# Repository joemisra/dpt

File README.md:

# dsp.coffee dpt - multifunction electron temple

** Fully built DPT module is currently unavailable, populated boards + panels are though - currently available at https://dsp.coffee/. In stock as of 2/17/2023. **

electrosmith daisy patch submodule based development platform

* 8 pots normalled to 0V - +5V.
* 8 CV in, this breaks normalled connection and pot acts as an attenuator.
* 2 gate in
* 2 gate out
* High fidelity stereo in/out (Daisy Patch Submodule uses the PCM3080 codec).
* 2 12-bit CV out from Daisy Patch Submodule, scaled to -5v to 10v
* 4 12-bit CV (or lofi audio w/ some hacking) from external DAC7554, scaled to -7v to 7v.
* TRS MIDI in/out (midi in uses lpzw auto-sensing circuit for type a/b)
* SD card slot.
* Expander header on the back for +5v, +3v3, SPI, UART, I2C, and USB connections. [Two expanders have been prototyped now, one with two tact switches and USB port, one with LED controller + 5 RGB leds and 4 tact switches]

Output scaling circuits for DAC7554 and TRS MIDI are based
on portions of https://github.com/plinkysynth/plinky-expander

Additional References
* https://www.electro-smith.com/daisy/patch-sm
* https://electro-smith.github.io/DaisySP/index.html
* https://electro-smith.github.io/libDaisy/index.html

Thx
* https://github.com/makingsoundmachines
* https://github.com/thisisnotrocketscience
* https://github.com/mmalex

BOM

|Designator|Package                                                                                                                                                                                                                 |Quantity                                   |Designation|Supplier and ref      |
|----------|------------------------------------------------------------------------------------------------------------------------------------------------------------------------------------------------------------------------|-------------------------------------------|-----------|----------------------|
|LED3,LED4 |3mm LED                                                                                                                                                                                                                 |2                                          ||                      |
|J*|Mono Thonkiconn                                                                                                                                                                                                         |22 
|JMIDIIN, JMIDIOUT|Stereo (Green) Thonkiconn                                                                                                                                                                                                         |2                    
|VRCV*|9mm Potentiometer (Alpha / Alps)                                                                                                                                                                                        |8                                          |10K        |                      |
|D4,D6,D5,D3,D8,D7|3mm LED (Bipolar Red / Green)                                                                                                                                                                                           |6                                          |LED_Dual_Bidirectional|Tayda                 |
|U_SDCARD1 |VERT_MICROSD_CENTERED                                                                                                                                                                                                   |1                                          || Mouser 945-PJS008U-3000-0 / Thonk |
|U9        |Electrosmith Daisy Patch Submodule                                                                                                                                                                                      |1                                          |ES_DAISY_PATCH_SM_REV1|                      | https://www.electro-smith.com/daisy/patch-sm
|R36,R35,R18,R16,
R17,R19|0603                                                                                                                                                                                                       |6                                          |1k         |                      |
|U11,U5,U10,U3,
U6,U4|SOIC-8                                                                                                                                                                                            |6                                          |TL072      |                      |
|C5,C4     |0603                                                                                                                                                                          |2                                          |100n       |                      |
|R9,R11,R10,R8|0603                                                                                                                                                                                                   |4                                          |56k        |                      |
|C2,C3     |C_Elec_4x5.4                                                                                                                                                                                                            |2                                          |47u        |                      |
|J_I2C1    |2x03 2.54mm_Vertical                                                                                                                                                                                         |1                                          ||                      |
|C11,C12,C13,C10,C18,C17|0603                                                                                                                                                                                                      |6                                          |1n         |                      |
|R22,R4,R7,R20,R29,
R30,R2,R6,R5|0603                                                                                                                                                                                                     |9                                          |10k        |                      |
|C14,C16,C6,C7,
C1,C8,C15,C9|0603                                                                                                                                                                                                     |8                                          |100n       |                      |
|R26,R34,R15,R24,
R33,R28,R27,R14,
R13,R25,R12|0603                                                                                                                                                                                                      |11                                         |220R       |                      |
|J14       |2x05 P2.54mm Vertical                                                                                                                                                                                         |1                                          ||                      |
|U2        |DAC7554IDGS                                                                                                                                                                                                  |1                                          ||                      |
|R32,R31   |0603                                                                                                                                                                                                      |2                                          |30k        |                      |
|R23,R21   |0603                                                                                                                                                                                                      |2                                          |4.7k       |                      |
|U8        |HCPL-0631 SOIC-8                                                                                                                                                                                               |1                                          |  |                      |
|U1        |LM4040DBZ-2.5 SOT-23                                                                                                                                                                                                                  |1                                          ||                      |
|J_EXPANDER2|2x08 P2.54mm Vertical                                                                                                                                                                                         |1                                          |USB_SPI_MUX_EXPANDER|                      |
|R1        |0603                                                                                                                                                                                                      |1                                          |3k         |                      |
|D2,D1     |1N1517 SOD-323                                                                                                                                                                                                               |2                                          |     |                      |
|R3        |0603                                                                                                                                                                                                      |1                                          |7.5k       |                      |
|U7        |SN74LVC1G17DBV SOT-23-5                                                                                                                                                                                                                |1                                          ||                      |

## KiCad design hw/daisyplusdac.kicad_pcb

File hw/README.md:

* Ultimately, assemble this however is most comfortable, but ensure that everything is flush.

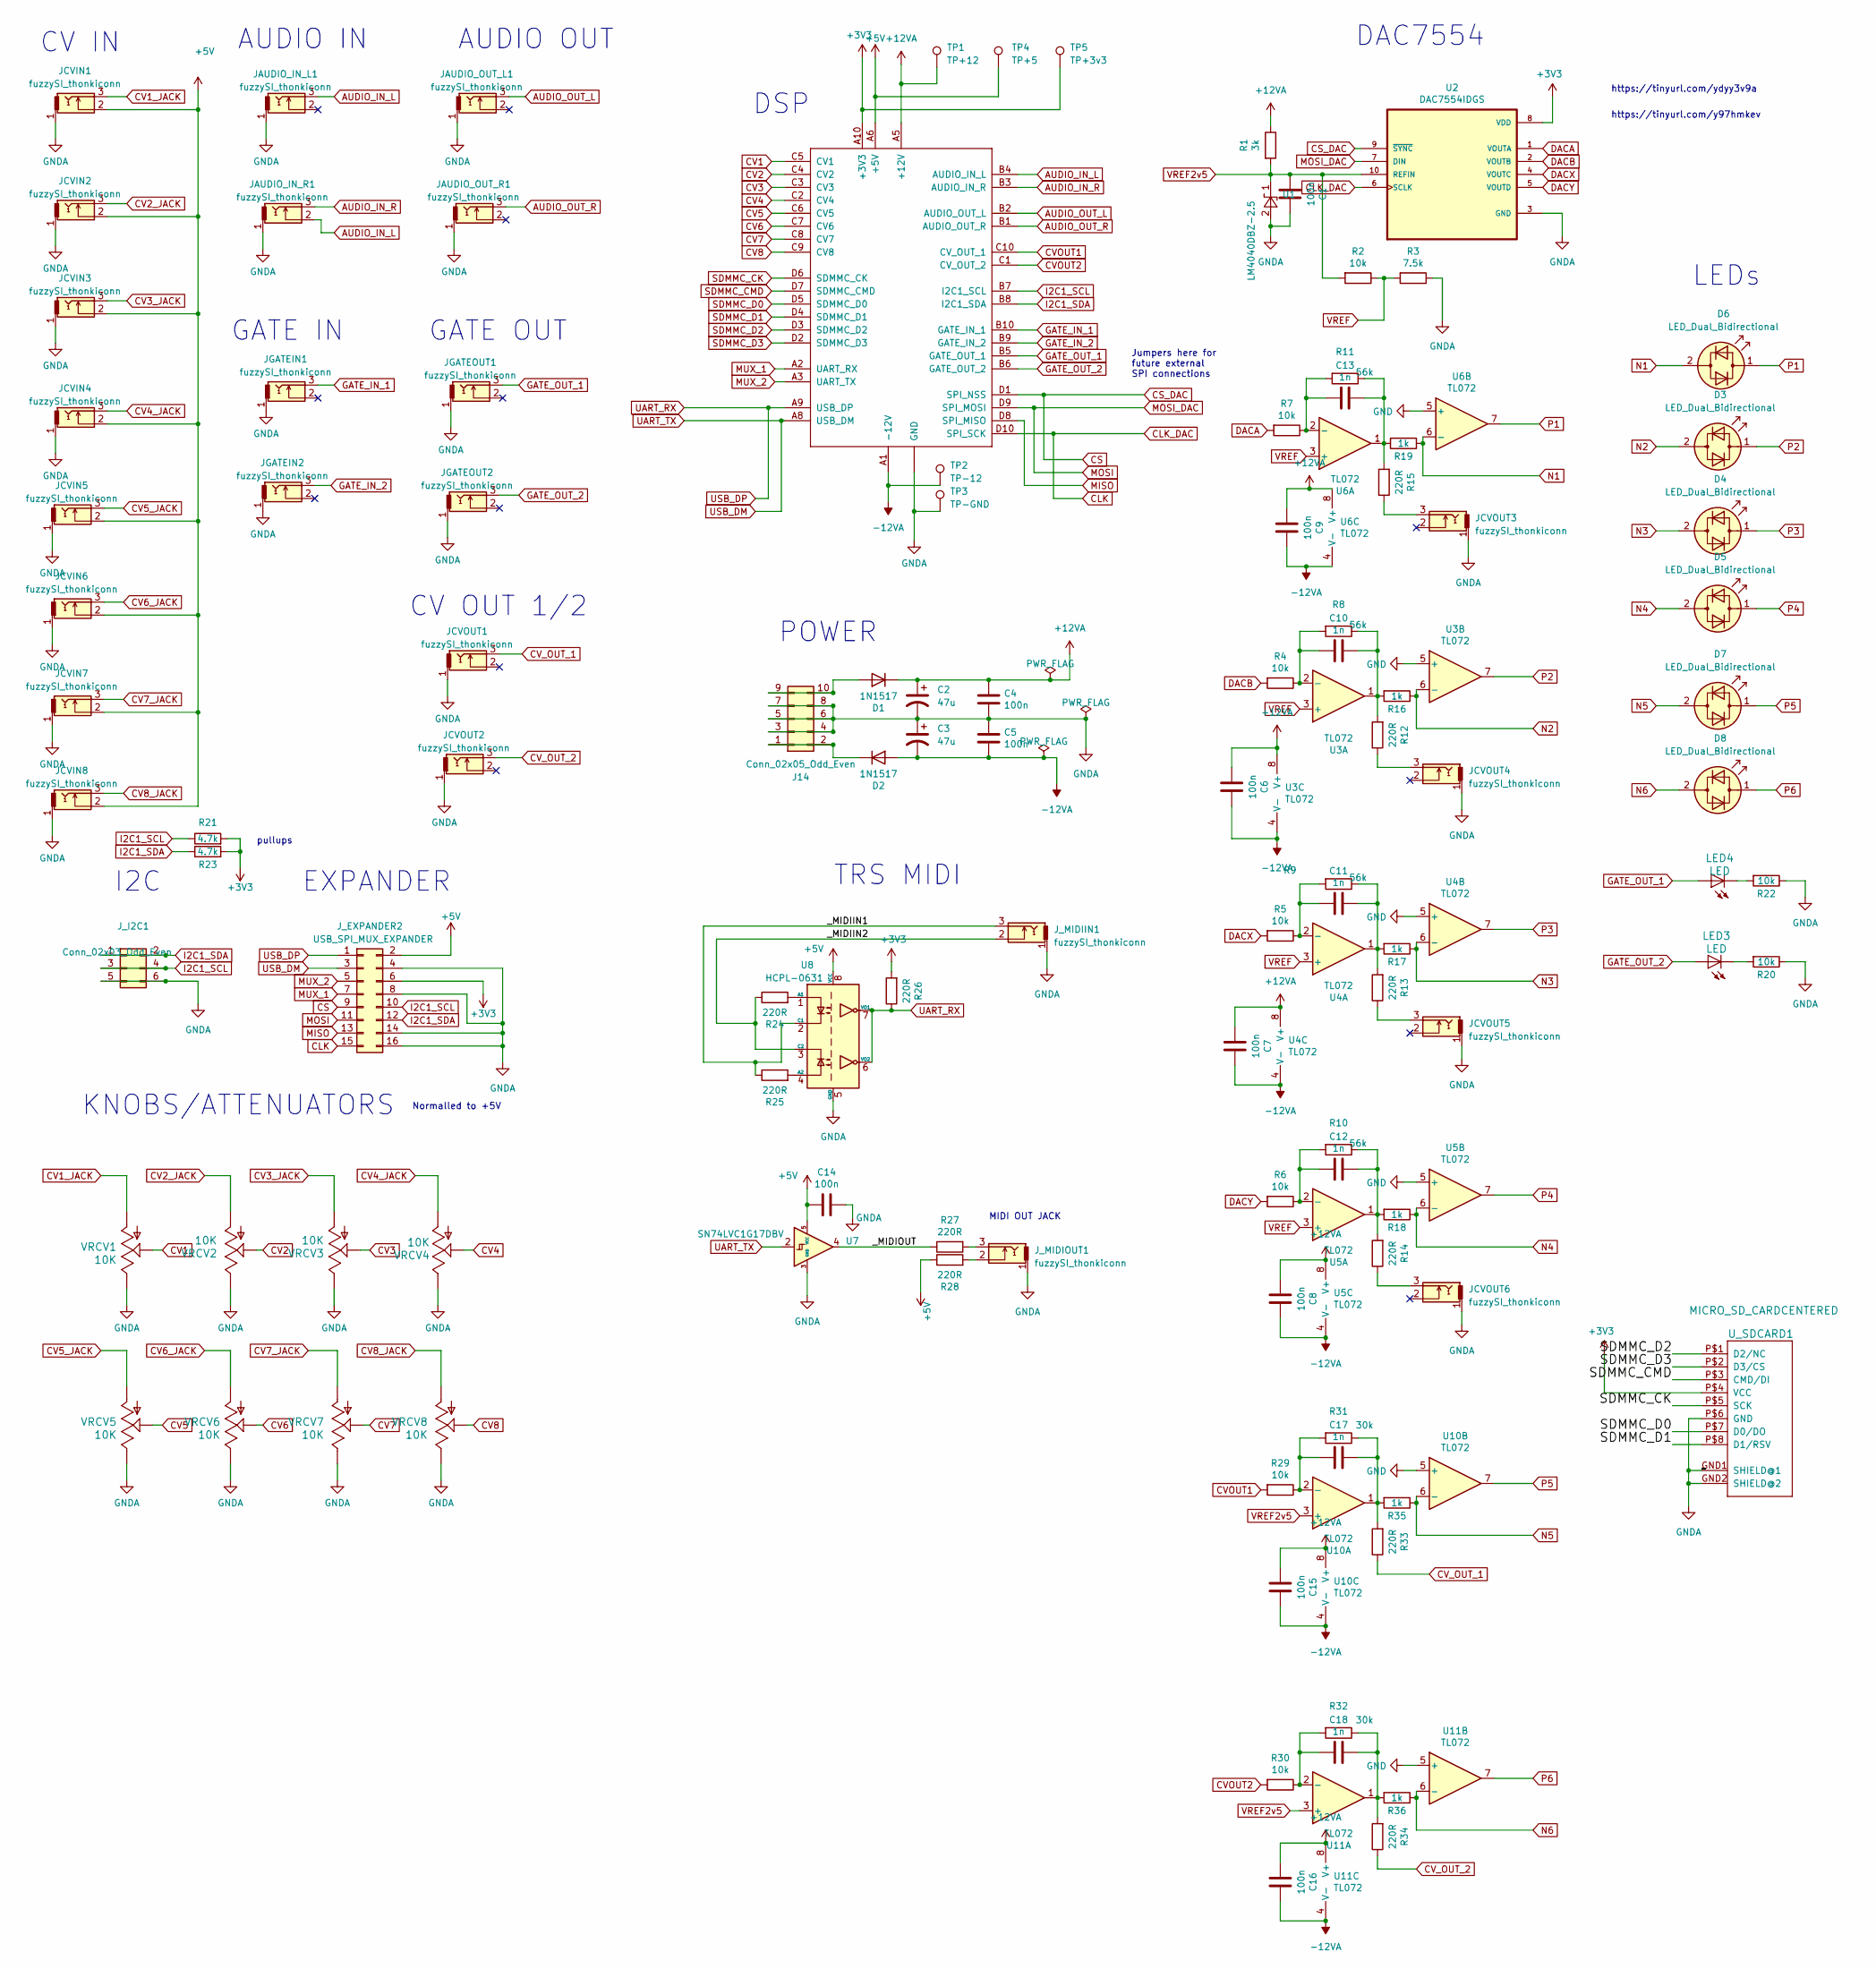
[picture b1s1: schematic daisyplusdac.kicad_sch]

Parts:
C1, C6, C7, C8, C9, C14, C15, C16: 100n; C_0603_1608Metric
C2, C3: 47u; C_Elec_4x5.4
C4, C5: 100n; C_0603_1608Metric_Pad1.08x0.95mm_HandSolder
C10, C11, C12, C13, C17, C18: 1n; C_0603_1608Metric
D1, D2: 1N1517; D_SOD-323
D3, D4, D5, D6, D7, D8: LED_Dual_Bidirectional; LED_D3.0mm
J14: Conn_02x05_Odd_Even; PinHeader_2x05_P2.54mm_Vertical
JAUDIO_IN_L1: fuzzySI_thonkiconn; thonkiconn_fuzzySi
JAUDIO_IN_R1: fuzzySI_thonkiconn; thonkiconn_fuzzySi
JAUDIO_OUT_L1: fuzzySI_thonkiconn; thonkiconn_fuzzySi
JAUDIO_OUT_R1: fuzzySI_thonkiconn; thonkiconn_fuzzySi
JCVIN1, JCVIN2, JCVIN3, JCVIN4, JCVIN5, JCVIN6, JCVIN7, JCVIN8: fuzzySI_thonkiconn; thonkiconn_fuzzySi
JCVOUT1, JCVOUT2, JCVOUT3, JCVOUT4, JCVOUT5, JCVOUT6: fuzzySI_thonkiconn; thonkiconn_fuzzySi
JGATEIN1, JGATEIN2: fuzzySI_thonkiconn; thonkiconn_fuzzySi
JGATEOUT1, JGATEOUT2: fuzzySI_thonkiconn; thonkiconn_fuzzySi
J_EXPANDER2: USB_SPI_MUX_EXPANDER; PinHeader_2x08_P2.54mm_Vertical
J_I2C1: Conn_02x03_Odd_Even; PinHeader_2x03_P2.54mm_Vertical
J_MIDIIN1: fuzzySI_thonkiconn; thonkiconn_fuzzySi
J_MIDIOUT1: fuzzySI_thonkiconn; thonkiconn_fuzzySi
LED3, LED4: LED
R1: 3k; R_0603_1608Metric
R2, R4, R5, R6, R7, R20, R22, R29, R30: 10k; R_0603_1608Metric
R3: 7.5k; R_0603_1608Metric
R8, R9, R10, R11: 56k; R_0603_1608Metric
R12, R13, R14, R15, R24, R25, R26, R27, R28, R33, R34: 220R; R_0603_1608Metric
R16, R17, R18, R19, R35, R36: 1k; R_0603_1608Metric
R21, R23: 4.7k; R_0603_1608Metric
R31, R32: 30k; R_0603_1608Metric
TP1: TP+12; TestPoint_Keystone_5000-5004_Miniature
TP2: TP-12; TestPoint_Keystone_5000-5004_Miniature
TP3: TP-GND; TestPoint_Keystone_5000-5004_Miniature
TP4: TP+5; TestPoint_Keystone_5000-5004_Miniature
TP5: TP+3v3; TestPoint_Keystone_5000-5004_Miniature
U1: LM4040DBZ-2.5; SOT-23
U2: DAC7554IDGS; MSOP-10_3x3mm_P0.5mm
U3, U4, U5, U6, U10, U11: TL072; SOIC-8_3.9x4.9mm_P1.27mm
U7: SN74LVC1G17DBV; SOT-23-5
U8: HCPL-0631; SOIC-8_3.9x4.9mm_P1.27mm
U9: ES_DAISY_PATCH_SM_REV1
U_SDCARD1: MICRO_SD_CARDCENTERED; VERT_MICROSD_CENTERED
VRCV1, VRCV2, VRCV3, VRCV4, VRCV5, VRCV6, VRCV7, VRCV8: 10K; Potentiometer_Alps_RK09K_Single_Vertical

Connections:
+3V3: J_EXPANDER2.6, R21.2, R23.2, R26.2, TP5.1, U2.8 (VDD), U9.A10 (+3V3), U_SDCARD1.P$4 (VCC)
+5V: C14.1, JCVIN1.2, JCVIN2.2, JCVIN3.2, JCVIN4.2, JCVIN5.2, JCVIN6.2, JCVIN7.2, JCVIN8.2, J_EXPANDER2.2, R28.1, TP4.1, U7.5 (VCC), U8.8 (VCC), U9.A6 (+5V)
+12VA: C2.1, C4.1, C6.1, C7.1, C8.1, C9.1, C15.1, C16.1, D1.1 (K), R1.1, TP1.1, U3.8 (V+), U4.8 (V+), U5.8 (V+), U6.8 (V+), U9.A5 (+12V), U10.8 (V+), U11.8 (V+)
-12VA: C3.2, C5.2, C6.2, C7.2, C8.2, C9.2, C15.2, C16.2, D2.2 (A), TP2.1, U3.4 (V-), U4.4 (V-), U5.4 (V-), U6.4 (V-), U9.A1 (-12V), U10.4 (V-), U11.4 (V-)
/_MIDIIN1: J_MIDIIN1.3, R25.1, U8.2 (C1)
/_MIDIIN2: J_MIDIIN1.2, R24.1, U8.3 (C2)
/_MIDIOUT: R27.1, U7.4
AUDIO_IN_L: JAUDIO_IN_L1.3, JAUDIO_IN_R1.2, U9.B4 (AUDIO_IN_L)
AUDIO_IN_R: JAUDIO_IN_R1.3, U9.B3 (AUDIO_IN_R)
AUDIO_OUT_L: JAUDIO_OUT_L1.3, U9.B2 (AUDIO_OUT_L)
AUDIO_OUT_R: JAUDIO_OUT_R1.3, U9.B1 (AUDIO_OUT_R)
CLK: J_EXPANDER2.15, U2.6 (SCLK), U9.D10 (SPI_SCK)
CS: J_EXPANDER2.9, U2.9 (~SYNC), U9.D1 (SPI_NSS)
CV1: U9.C5 (CV1), VRCV1.2
CV1_JACK: JCVIN1.3, VRCV1.1
CV2: U9.C4 (CV2), VRCV2.2
CV2_JACK: JCVIN2.3, VRCV2.1
CV3: U9.C3 (CV3), VRCV3.2
CV3_JACK: JCVIN3.3, VRCV3.1
CV4: U9.C2 (CV4), VRCV4.2
CV4_JACK: JCVIN4.3, VRCV4.1
CV5: U9.C6 (CV5), VRCV5.2
CV5_JACK: JCVIN5.3, VRCV5.1
CV6: U9.C7 (CV6), VRCV6.2
CV6_JACK: JCVIN6.3, VRCV6.1
CV7: U9.C8 (CV7), VRCV7.2
CV7_JACK: JCVIN7.3, VRCV7.1
CV8: U9.C9 (CV8), VRCV8.2
CV8_JACK: JCVIN8.3, VRCV8.1
CVOUT1: R29.2, U9.C10 (CV_OUT_1)
CVOUT2: R30.2, U9.C1 (CV_OUT_2)
CV_OUT_1: JCVOUT1.3, R33.1
CV_OUT_2: JCVOUT2.3, R34.1
DACA: R7.2, U2.1 (VOUTA)
DACB: R4.2, U2.2 (VOUTB)
DACX: R5.2, U2.4 (VOUTC)
DACY: R6.2, U2.5 (VOUTD)
GATE_IN_1: JGATEIN1.3, U9.B10 (GATE_IN_1)
GATE_IN_2: JGATEIN2.3, U9.B9 (GATE_IN_2)
GATE_OUT_1: JGATEOUT1.3, LED4.A, U9.B5 (GATE_OUT_1)
GATE_OUT_2: JGATEOUT2.3, LED3.A, U9.B6 (GATE_OUT_2)
GND: C1.1, C2.2, C3.1, C4.2, C5.1, C14.2, J14.3, J14.4, J14.5, J14.6, J14.7, J14.8, JAUDIO_IN_L1.1, JAUDIO_IN_R1.1, JAUDIO_OUT_L1.1, JAUDIO_OUT_R1.1, JCVIN1.1, JCVIN2.1, JCVIN3.1, JCVIN4.1, JCVIN5.1, JCVIN6.1, JCVIN7.1, JCVIN8.1, JCVOUT1.1, JCVOUT2.1, JCVOUT3.1, JCVOUT4.1, JCVOUT5.1, JCVOUT6.1, JGATEIN1.1, JGATEIN2.1, JGATEOUT1.1, JGATEOUT2.1, J_EXPANDER2.4, J_EXPANDER2.8, J_EXPANDER2.14, J_EXPANDER2.16, J_I2C1.5, J_I2C1.6, J_MIDIIN1.1, J_MIDIOUT1.1, R3.1, R20.1, R22.1, TP3.1, U1.2 (A), U2.3 (GND), U3.5 (+), U4.5 (+), U5.5 (+), U6.5 (+), U7.3 (GND), U8.5 (GND), U9.A4 (GND), U9.A7 (GND), U10.5 (+), U11.5 (+), U_SDCARD1.GND1 (SHIELD@1), U_SDCARD1.GND2 (SHIELD@2), U_SDCARD1.P$6 (GND), VRCV1.3, VRCV2.3, VRCV3.3, VRCV4.3, VRCV5.3, VRCV6.3, VRCV7.3, VRCV8.3
I2C1_SCL: J_EXPANDER2.10, J_I2C1.3, J_I2C1.4, R21.1, U9.B7 (I2C1_SCL)
I2C1_SDA: J_EXPANDER2.12, J_I2C1.1, J_I2C1.2, R23.1, U9.B8 (I2C1_SDA)
MISO: J_EXPANDER2.13, U9.D8 (SPI_MISO)
MOSI: J_EXPANDER2.11, U2.7 (DIN), U9.D9 (SPI_MOSI)
MUX_1: J_EXPANDER2.7, U9.A2 (UART_RX)
MUX_2: J_EXPANDER2.5, U9.A3 (UART_TX)
N1: D6.2 (AK), R19.1, U6.6 (-)
N2: D3.2 (AK), R16.1, U3.6 (-)
N3: D4.2 (AK), R17.1, U4.6 (-)
N4: D5.2 (AK), R18.1, U5.6 (-)
N5: D7.2 (AK), R35.1, U10.6 (-)
N6: D8.2 (AK), R36.1, U11.6 (-)
unnamed: C10.1, R8.1, R12.2, R16.2, U3.1
unnamed: C11.1, R9.1, R13.2, R17.2, U4.1
unnamed: C12.1, R10.1, R14.2, R18.2, U5.1
unnamed: C13.1, R11.1, R15.2, R19.2, U6.1
unnamed: C17.1, R31.1, R33.2, R35.2, U10.1
unnamed: C18.1, R32.1, R34.2, R36.2, U11.1
unnamed: D1.2 (A), J14.9, J14.10
unnamed: D2.1 (K), J14.1, J14.2
unnamed: JCVOUT3.3, R15.1
unnamed: JCVOUT4.3, R12.1
unnamed: JCVOUT5.3, R13.1
unnamed: JCVOUT6.3, R14.1
unnamed: J_MIDIOUT1.2, R28.2
unnamed: J_MIDIOUT1.3, R27.2
unnamed: LED3.K (C), R20.2
unnamed: LED4.K (C), R22.2
unnamed: C10.2, R4.1, R8.2, U3.2 (-)
unnamed: C11.2, R5.1, R9.2, U4.2 (-)
unnamed: C12.2, R6.1, R10.2, U5.2 (-)
unnamed: C13.2, R7.1, R11.2, U6.2 (-)
unnamed: R24.2, U8.1 (A1)
unnamed: R25.2, U8.4 (A2)
unnamed: C17.2, R29.1, R31.2, U10.2 (-)
unnamed: C18.2, R30.1, R32.2, U11.2 (-)
P1: D6.1 (KA), U6.7
P2: D3.1 (KA), U3.7
P3: D4.1 (KA), U4.7
P4: D5.1 (KA), U5.7
P5: D7.1 (KA), U10.7
P6: D8.1 (KA), U11.7
SDMMC_CK: U9.D6 (SDMMC_CK), U_SDCARD1.P$5 (SCK)
SDMMC_CMD: U9.D7 (SDMMC_CMD), U_SDCARD1.P$3 (CMD/DI)
SDMMC_D0: U9.D5 (SDMMC_D0), U_SDCARD1.P$7 (D0/DO)
SDMMC_D1: U9.D4 (SDMMC_D1), U_SDCARD1.P$8 (D1/RSV)
SDMMC_D2: U9.D3 (SDMMC_D2), U_SDCARD1.P$1 (D2/NC)
SDMMC_D3: U9.D2 (SDMMC_D3), U_SDCARD1.P$2 (D3/CS)
UART_RX: J_EXPANDER2.1, R26.1, U8.6 (VO2), U8.7 (VO1), U9.A9 (USB_DP)
UART_TX: J_EXPANDER2.3, U7.2, U9.A8 (USB_DM)
VREF: R2.1, R3.2, U3.3 (+), U4.3 (+), U5.3 (+), U6.3 (+)
VREF2v5: C1.2, R1.2, R2.2, U1.1 (K), U2.10 (REFIN), U10.3 (+), U11.3 (+)

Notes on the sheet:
DSP
CV IN
EXPANDER
AUDIO OUT
Jumpers here for future external SPI connections
POWER
DAC7554
TRS MIDI
MIDI OUT JACK
pullups
https://tinyurl.com/ydyy3v9a
KNOBS/ATTENUATORS
I2C
https://tinyurl.com/y97hmkev
CV OUT 1/2
GATE OUT
GATE IN
AUDIO IN
LEDs
Normalled to +5V

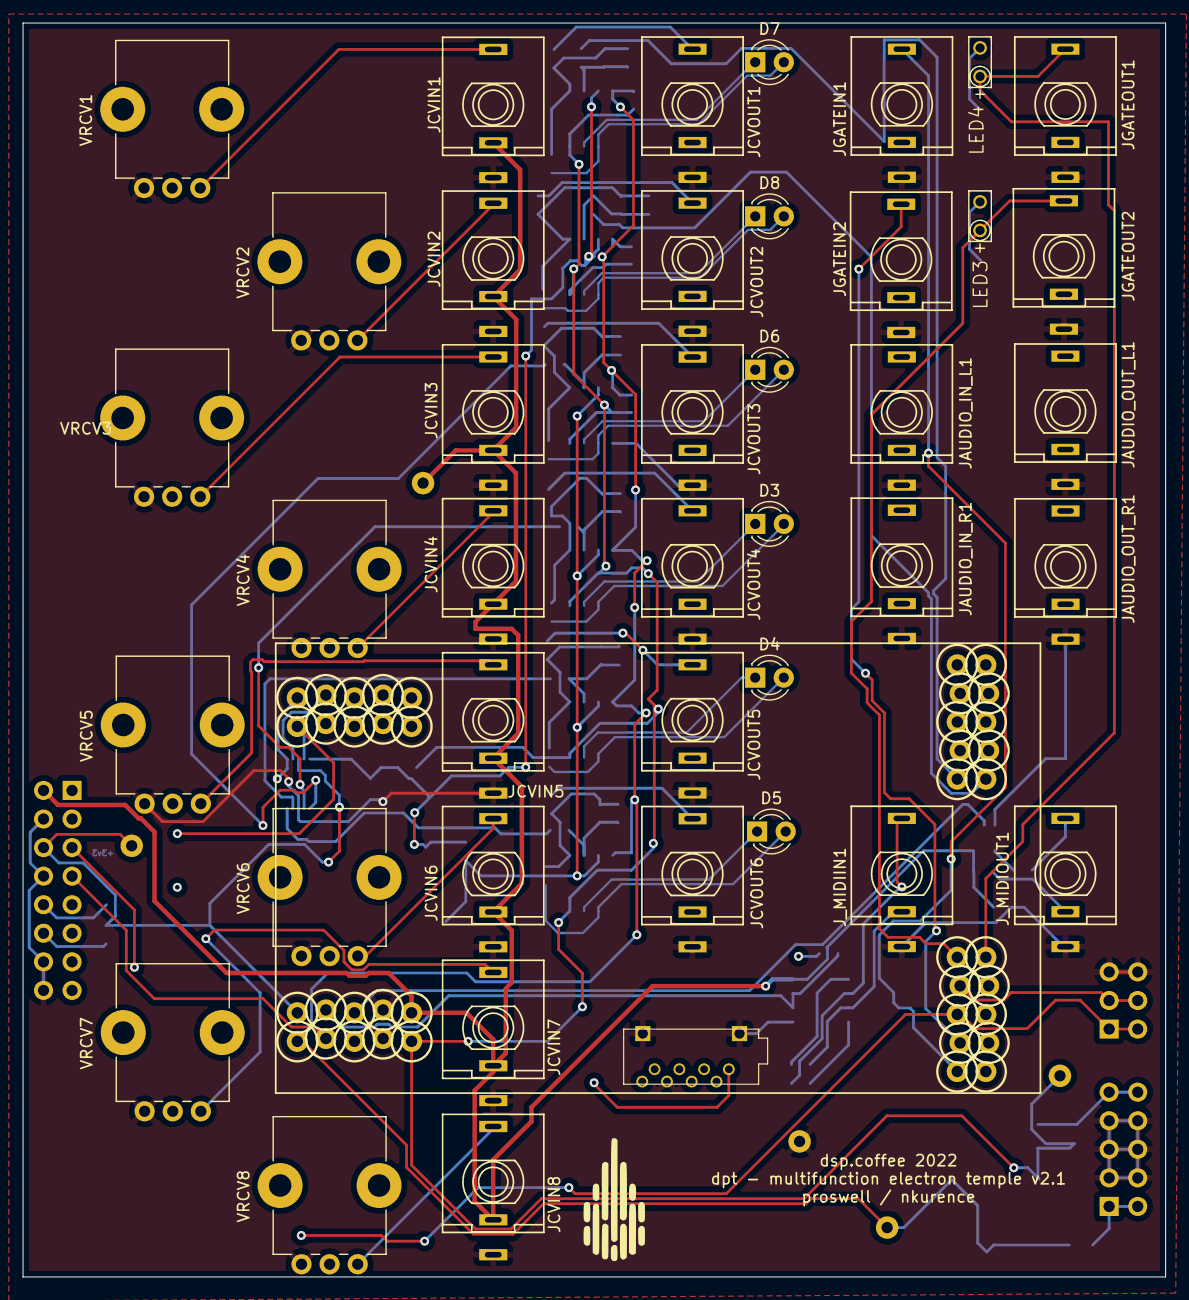
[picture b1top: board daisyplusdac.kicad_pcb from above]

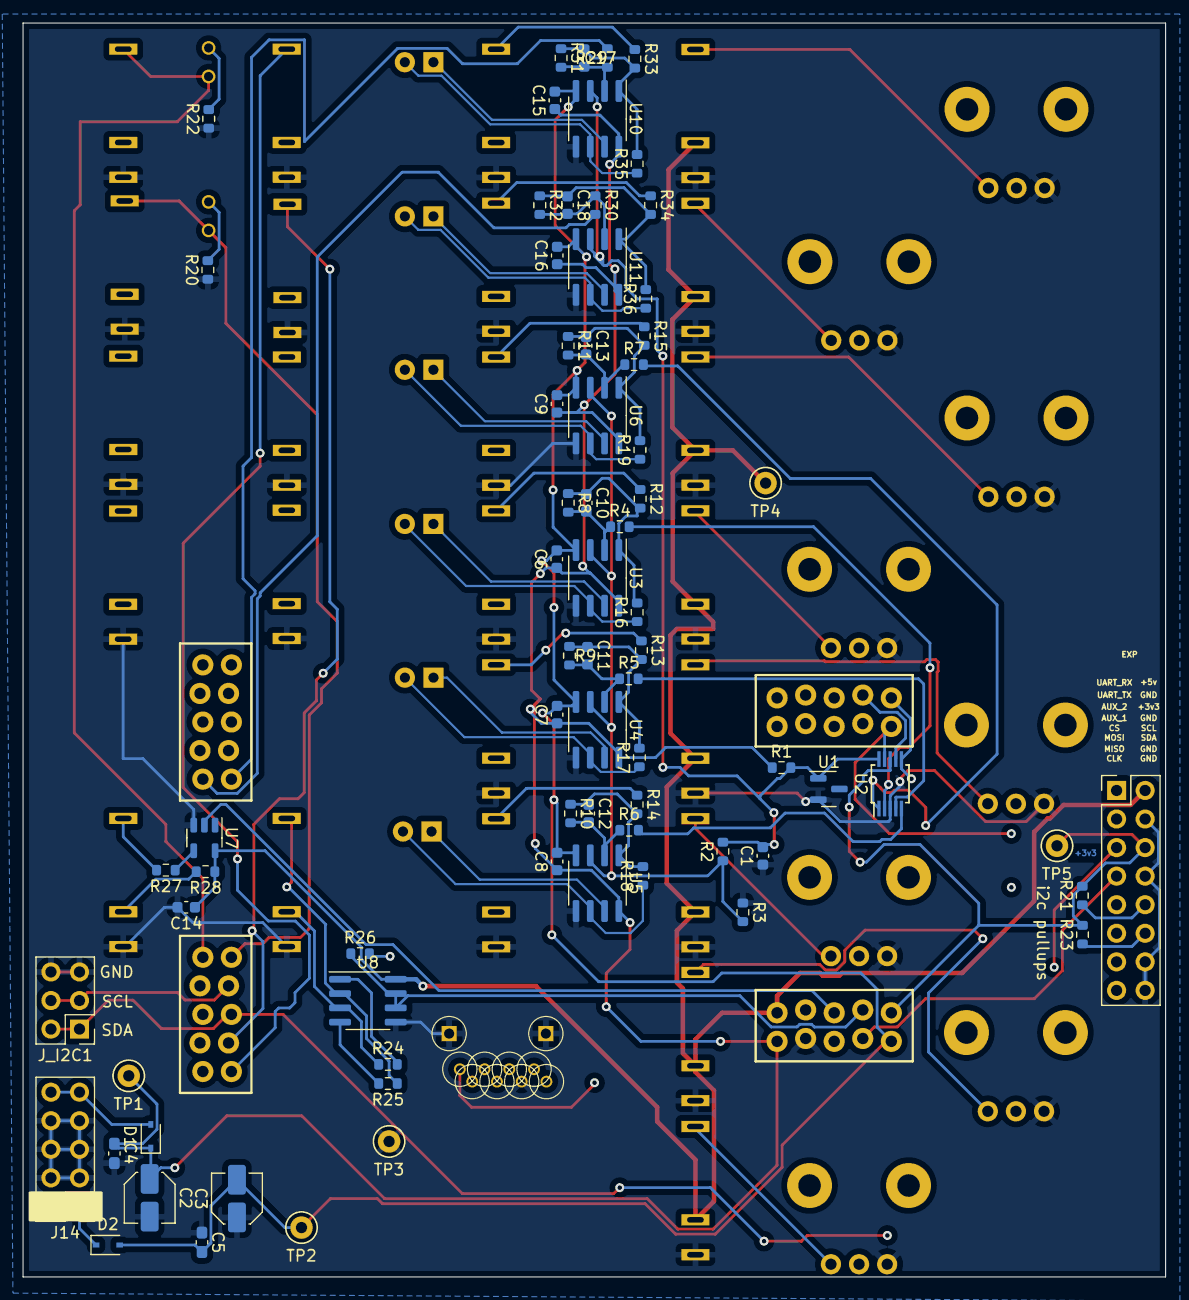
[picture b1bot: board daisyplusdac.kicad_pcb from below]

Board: 4 copper layers, 101.6 x 111.5 mm, 116 parts (74 on the bottom side), 94 nets.

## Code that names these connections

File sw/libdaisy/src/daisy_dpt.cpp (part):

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        user_led.pull = DSY_GPIO_NOPULL;
        user_led.pin  = PIN_USER_LED;
        dsy_gpio_init(&user_led);
        //gate_in_1.Init((dsy_gpio_pin *)&DPT::B10);
        gate_in_1.Init((dsy_gpio_pin *)&B10);
        gate_in_2.Init((dsy_gpio_pin *)&B9);

        gate_out_1.mode = DSY_GPIO_MODE_OUTPUT_PP;
        gate_out_1.pull = DSY_GPIO_NOPULL;
        gate_out_1.pin  = B6;
        dsy_gpio_init(&gate_out_1);

        gate_out_2.mode = DSY_GPIO_MODE_OUTPUT_PP;
        gate_out_2.pull = DSY_GPIO_NOPULL;
        gate_out_2.pin  = B5;
        dsy_gpio_init(&gate_out_2);

        /** DAC init */
        pimpl_->InitDac();
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
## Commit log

2022-04-03 Uploading initial work files
2022-04-03 Added BOM
2022-04-09 restructuring project, libdaisy + daisysp as submodules, beginning HardwareTest mods for DPT
2022-04-09 removed extra old libdaisy directory
2022-04-17 adding basic i2c leader example
2022-04-21 added support for raw output, some comments
2022-04-21 comments
2022-05-01 some refactoring, separated out voice code
2022-05-01 add gitignore
2022-05-01 importing megabasic midi polysynth
2022-05-04 various tweaks
2022-05-07 changes to use libdaisy 5.0 timer code
2022-05-09 added some gpio setup for 2 external buttons, uses usb/midi pins
2022-05-17 attempting to fix libdaisy submodule ref
2022-05-17 attempting again to update libdaisy to current ver
2022-05-20 spi / timer stuff
2022-05-20 updated to use DMA calls w/ SPI
2022-05-20 example updates
2022-05-24 Initial import for template project.
2022-05-24 Had accidentally left usb MIDI attempt in, this did not work yet
2022-05-24 Updates for MIDI Polysynth Example "MegaBasic"
2022-05-24 Straight port of patch_sm reverb example.
2022-09-17 incorrectly committed an incomplete main file, fixing
2022-09-17 added some comments and a boundary check
2022-09-17 Folded in ReverbSc for audio testing.
2022-11-27 removed extra inversion in WriteCvOutExp
2023-02-17 fix thonki qty
2025-08-04 Add files via upload
    claude generated v1, may have errors
2025-08-05 Update dpt-documentation.md again
2025-08-05 removed incorrect expansion header details
